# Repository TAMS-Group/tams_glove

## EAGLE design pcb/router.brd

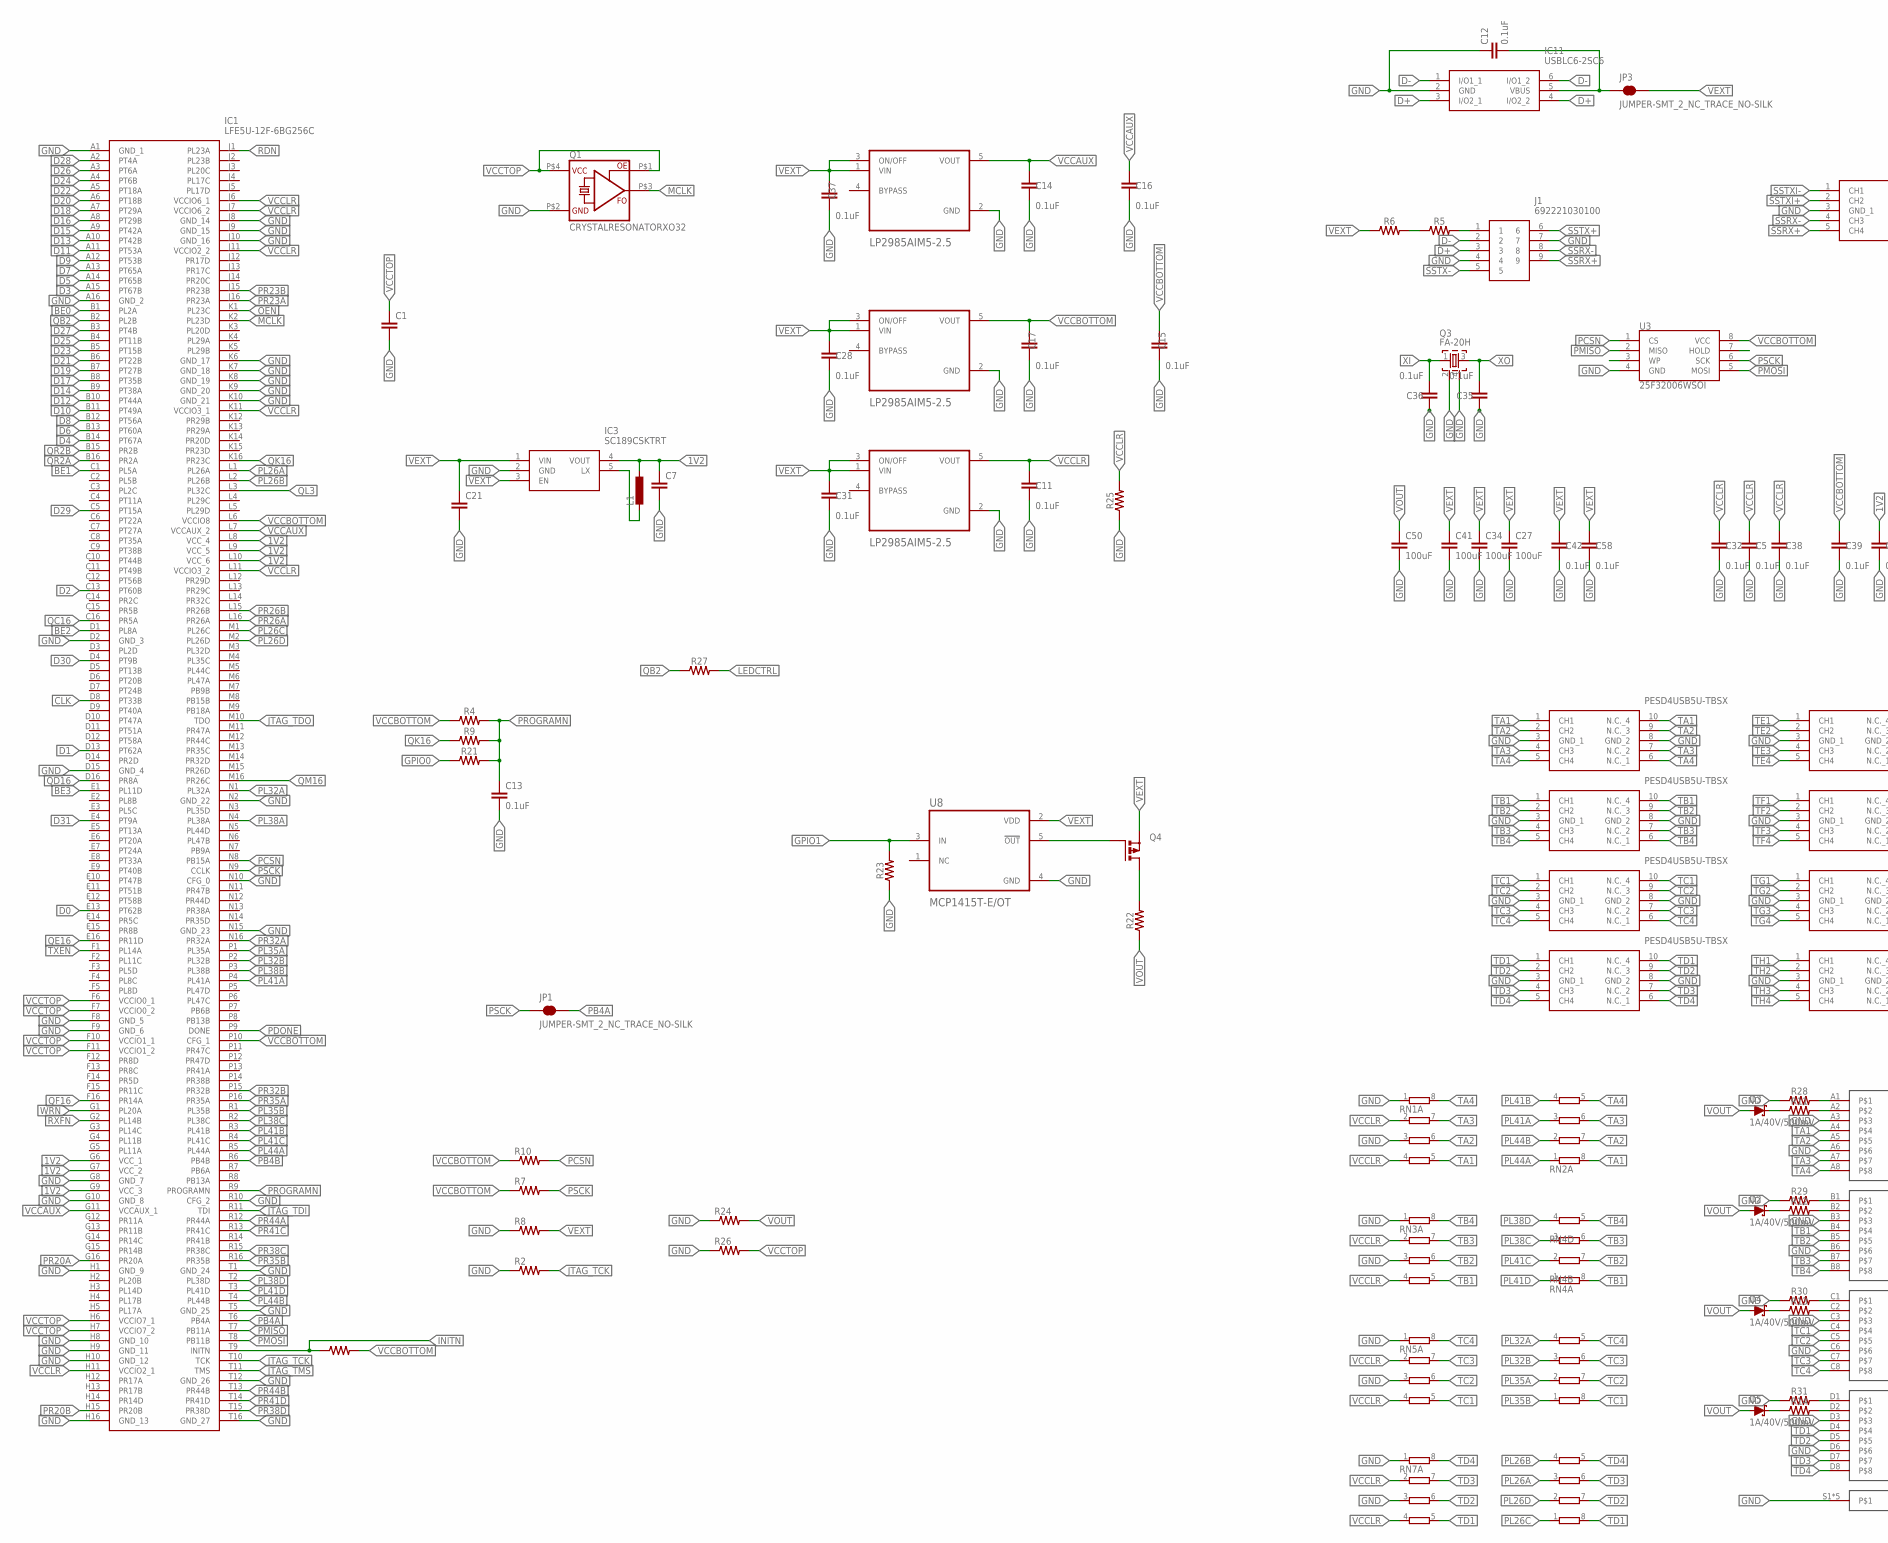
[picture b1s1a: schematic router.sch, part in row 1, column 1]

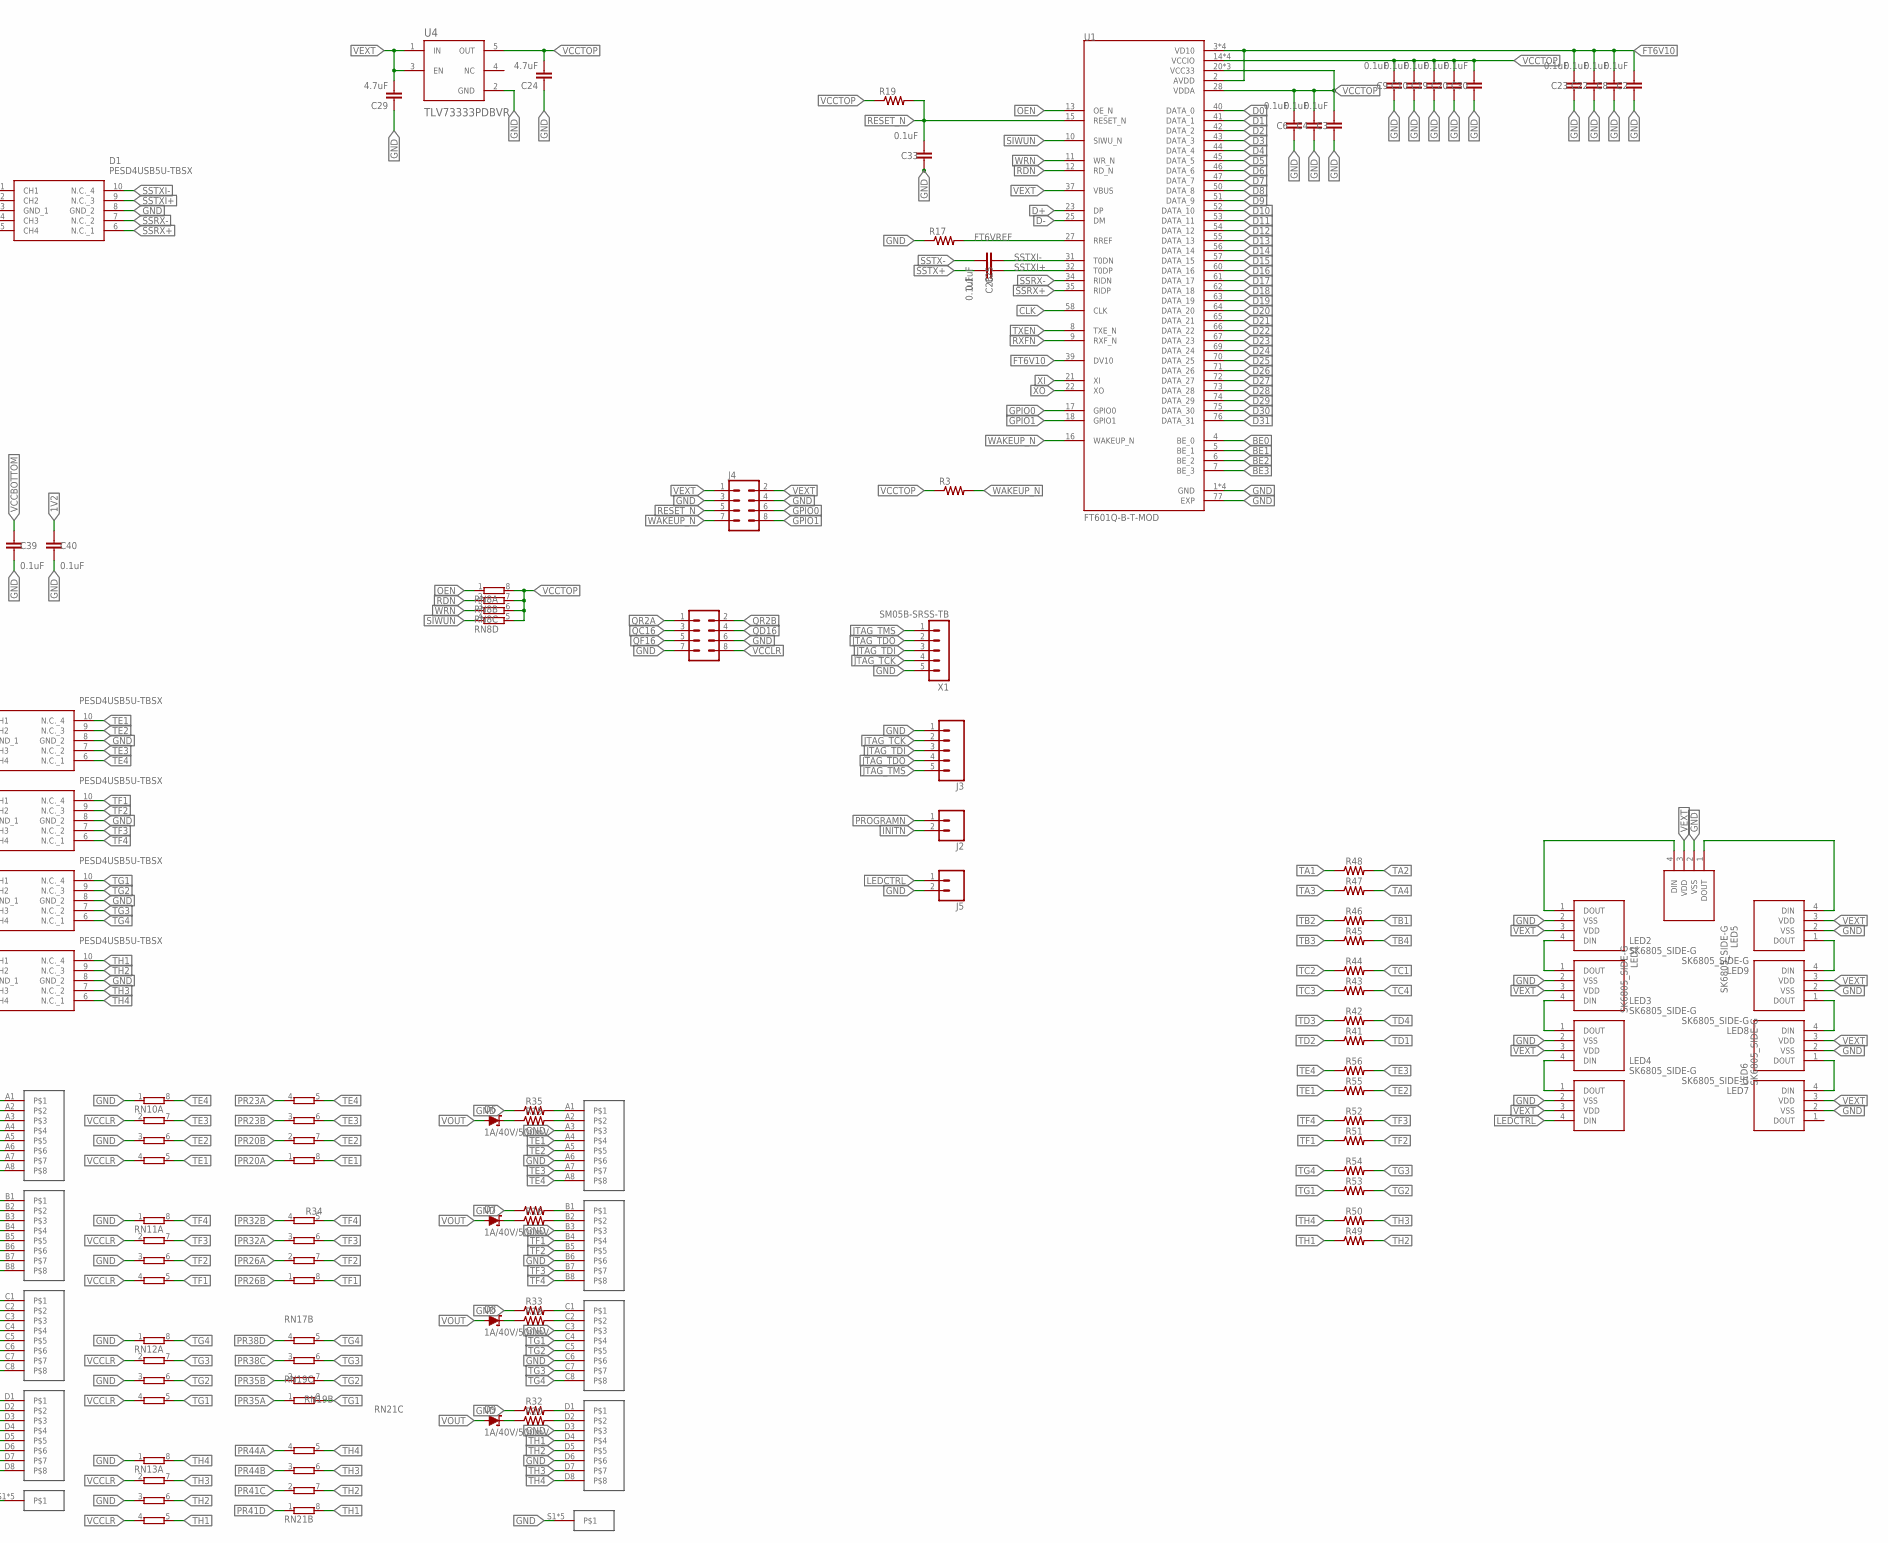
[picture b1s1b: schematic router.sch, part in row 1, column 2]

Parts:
C1: C-EUC0603; C0603
C2, C3, C4, C5, C6, C8, C9, C10, C11, C12, C13, C14, C15, C16, C17, C19, C20, C22, C23, C25, C26, C28, C30, C31, C32, C33, C35, C36, C37, C38, C39, C40, C42, C58: 0.1uF; 0603
C7, C21: C-EUC0805; C0805
C24, C29: 4.7uF; C0603
C27, C34, C41, C50: 100uF; C1210
D1, D10, D11, D12, D13, D14, D15, D16, D17: PESD4USB5U-TBSX; SON50P100X250X80-10N
D2, D3, D4, D5, D6, D7, D8, D9: 1A/40V/500mV; SMA-DIODE
IC1: LFE5U-12F-6BG256C; BGA256C80P16X16_1400X1400X170
IC3: SC189CSKTRT; SOT95P280X145-5N
IC11: USBLC6-2SC6; SOT95P280X145-6N
J1: 692221030100; WR-COM_USB_TYPE_B
J2, J5: CONN_02; 1X02
J3: CONN_05; 1X05
J4, J8: CONN_04X2; 2X4
JP1, JP3: JUMPER-SMT_2_NC_TRACE_NO-SILK; SMT-JUMPER_2_NC_TRACE_NO-SILK
L1: L-EUL3230M; L3230M
LED1, LED2, LED3, LED4, LED5, LED6, LED7, LED8, LED9: SK6805_SIDE-G; SK6805SIDEG
Q1: CRYSTALRESONATORXO32; XO32
Q3: FA-20H
Q4: P-MOSFET-SO8; SO-08
R1, R2, R3, R4, R7, R8, R9, R10, R17, R19, R21, R23, R24, R25, R26, R27, R28, R29, R30, R31, R32, R33, R34, R35: 0603
R5, R6, R11, R12, R13, R14, R15, R16, R18, R20: 0805
R22: 1206
R41, R42, R43, R44, R45, R46, R47, R48, R49, R50, R51, R52, R53, R54, R55, R56: 0402
RN1, RN2, RN3, RN4, RN5, RN6, RN7, RN8, RN9, RN10, RN11, RN12, RN13, RN15, RN17, RN19, RN21: 4R-NEXBV8V; EXBV8V
U1: FT601Q-B-T-MOD; QFN40P900X900X100-77N-MOD
U3: 25F32006WSOI; SO08-EIAJ
U4: TLV73333PDBVR; SOT95P280X145-5N
U5, U6, U7: LP2985AIM5-2.5; SOT95P280X145-5N
U8: MCP1415T-E/OT; SOT95P270X145-5N
U$49, U$50: QUADRJ45; ARJ14A-MESA-MU2_CONN_ARJ14A-MESA-MU2
X1: SM05B-SRSS-TB

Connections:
1V2: C7.1, C40.1, IC1.G6 (VCC_1), IC1.G7 (VCC_2), IC1.G9 (VCC_3), IC1.L8 (VCC_4), IC1.L9 (VCC_5), IC1.L10 (VCC_6), IC3.4 (VOUT), L1.1
BE0: IC1.B1 (PL2A), U1.4 (BE_0)
BE1: IC1.C1 (PL5A), U1.5 (BE_1)
BE2: IC1.D1 (PL8A), U1.6 (BE_2)
BE3: IC1.E1 (PL11D), U1.7 (BE_3)
CLK: IC1.D8 (PT33B), U1.58 (CLK)
D0: IC1.E13 (PT62B), U1.40 (DATA_0)
D1: IC1.D13 (PT62A), U1.41 (DATA_1)
D2: IC1.C13 (PT60B), U1.42 (DATA_2)
D3: IC1.A15 (PT67B), U1.43 (DATA_3)
D4: IC1.B14 (PT67A), U1.44 (DATA_4)
D5: IC1.A14 (PT65B), U1.45 (DATA_5)
D6: IC1.B13 (PT60A), U1.46 (DATA_6)
D7: IC1.A13 (PT65A), U1.47 (DATA_7)
D8: IC1.B12 (PT56A), U1.50 (DATA_8)
D9: IC1.A12 (PT53B), U1.51 (DATA_9)
D10: IC1.B11 (PT49A), U1.52 (DATA_10)
D11: IC1.A11 (PT53A), U1.53 (DATA_11)
D12: IC1.B10 (PT44A), U1.54 (DATA_12)
D13: IC1.A10 (PT42B), U1.55 (DATA_13)
D14: IC1.B9 (PT38A), U1.56 (DATA_14)
D15: IC1.A9 (PT42A), U1.57 (DATA_15)
D16: IC1.A8 (PT29B), U1.60 (DATA_16)
D17: IC1.B8 (PT35B), U1.61 (DATA_17)
D18: IC1.A7 (PT29A), U1.62 (DATA_18)
D19: IC1.B7 (PT27B), U1.63 (DATA_19)
D20: IC1.A6 (PT18B), U1.64 (DATA_20)
D21: IC1.B6 (PT22B), U1.65 (DATA_21)
D22: IC1.A5 (PT18A), U1.66 (DATA_22)
D23: IC1.B5 (PT15B), U1.67 (DATA_23)
D24: IC1.A4 (PT6B), U1.69 (DATA_24)
D25: IC1.B4 (PT11B), U1.70 (DATA_25)
D26: IC1.A3 (PT6A), U1.71 (DATA_26)
D27: IC1.B3 (PT4B), U1.72 (DATA_27)
D28: IC1.A2 (PT4A), U1.73 (DATA_28)
D29: IC1.C5 (PT15A), U1.74 (DATA_29)
D30: IC1.D4 (PT9B), U1.75 (DATA_30)
D31: IC1.E4 (PT9A), U1.76 (DATA_31)
D+: IC11.3 (I/O2_1), IC11.4 (I/O2_2), J1.3, U1.23 (DP)
D-: IC11.1 (I/O1_1), IC11.6 (I/O1_2), J1.2, U1.25 (DM)
FT6V10: C2.2, C8.2, C22.2, C23.2, U1.2 (AVDD), U1.3 (VD10), U1.30 (VD10), U1.33 (VD10), U1.39 (DV10), U1.48 (VD10)
FT6VREF: R17.2, U1.27 (RREF)
GND: C1.2, C2.1, C3.1, C4.1, C5.2, C6.1, C7.2, C8.1, C9.1, C10.1, C11.2, C12.1, C13.2, C14.2, C15.2, C16.2, C17.2, C19.1, C20.1, C21.2, C22.1, C23.1, C24.1, C27.2, C28.2, C29.1, C30.1, C31.2, C32.2, C33.1, C34.2, C35.1, C36.1, C37.2, C38.2, C39.2, C40.2, C41.2, C42.2, C50.2, C58.2, D1.3 (GND_1), D1.8 (GND_2), D10.3 (GND_1), D10.8 (GND_2), D11.3 (GND_1), D11.8 (GND_2), D12.3 (GND_1), D12.8 (GND_2), D13.3 (GND_1), D13.8 (GND_2), D14.3 (GND_1), D14.8 (GND_2), D15.3 (GND_1), D15.8 (GND_2), D16.3 (GND_1), D16.8 (GND_2), D17.3 (GND_1), D17.8 (GND_2), IC1.A1 (GND_1), IC1.A16 (GND_2), IC1.D2 (GND_3), IC1.D15 (GND_4), IC1.F8 (GND_5), IC1.F9 (GND_6), IC1.G8 (GND_7), IC1.G10 (GND_8), IC1.H1 (GND_9), IC1.H8 (GND_10), IC1.H9 (GND_11), IC1.H10 (GND_12), IC1.H16 (GND_13), IC1.J8 (GND_14), IC1.J9 (GND_15), IC1.J10 (GND_16), IC1.K6 (GND_17), IC1.K7 (GND_18), IC1.K8 (GND_19), IC1.K9 (GND_20), IC1.K10 (GND_21), IC1.N2 (GND_22), IC1.N10 (CFG_0), IC1.N15 (GND_23), IC1.R10 (CFG_2), IC1.T1 (GND_24), IC1.T5 (GND_25), IC1.T12 (GND_26), IC1.T16 (GND_27), IC3.2 (GND), IC11.2 (GND), J1.4, J1.7, J3.1, J4.3, J4.4, J5.2, J8.6, J8.7, LED1.2 (VSS), LED2.2 (VSS), LED3.2 (VSS), LED4.2 (VSS), LED5.2 (VSS), LED6.2 (VSS), LED7.2 (VSS), LED8.2 (VSS), LED9.2 (VSS), Q1.P$2 (GND), Q3.2, Q3.4, R2.1, R8.1, R17.1, R23.1, R24.1, R25.1, R26.1, R28.1, R29.1, R30.1, R31.1, R32.1, R33.1, R34.1, R35.1, RN1.1, RN1.3 (1), RN3.1, RN3.3 (1), RN5.1, RN5.3 (1), RN7.1, RN7.3 (1), RN10.1, RN10.3 (1), RN11.1, RN11.3 (1), RN12.1, RN12.3 (1), RN13.1, RN13.3 (1), U1.1 (GND), U1.26 (GND), U1.29 (GND), U1.36 (GND), U1.77 (EXP), U3.4 (GND), U4.2 (GND), U5.2 (GND), U6.2 (GND), U7.2 (GND), U8.4 (GND), U$49.A3, U$49.A6, U$49.B3, U$49.B6, U$49.C3, U$49.C6, U$49.D3, U$49.D6, U$49.S1, U$49.S2, U$49.S3, U$49.S4, U$49.S5, U$50.A3, U$50.A6, U$50.B3, U$50.B6, U$50.C3, U$50.C6, U$50.D3, U$50.D6, U$50.S1, U$50.S2, U$50.S3, U$50.S4, U$50.S5, X1.5
GPIO0: J4.6, R21.1, U1.17 (GPIO0)
GPIO1: J4.8, R23.2, U1.18 (GPIO1), U8.3 (IN)
INITN: IC1.T9 (INITN), J2.2, R1.1
JTAG_TCK: IC1.T10 (TCK), J3.2, R2.2, X1.4
JTAG_TDI: IC1.R11 (TDI), J3.3, X1.3
JTAG_TDO: IC1.M10 (TDO), J3.4, X1.2
JTAG_TMS: IC1.T11 (TMS), J3.5, X1.1
LEDCTRL: J5.1, LED4.4 (DIN), R27.2
MCLK: IC1.K2 (PL23D), Q1.P$3 (FO)
unnamed: R15.2, U$50.A2
unnamed: R16.2, U$50.B2
unnamed: IC3.5 (LX), L1.2
unnamed: R18.2, U$50.C2
unnamed: R20.2, U$50.D2
unnamed: R35.2, U$50.A1
unnamed: C12.2, IC11.5 (VBUS), JP3.1
unnamed: R5.1, R6.2
unnamed: J1.1, R5.2
unnamed: Q4.4 (G), U8.5 (!OUT)
unnamed: Q4.5 (D), Q4.6 (D), Q4.7 (D), Q4.8 (D), R22.2
unnamed: R34.2, U$50.B1
unnamed: R33.2, U$50.C1
unnamed: LED1.4 (DIN), LED2.1 (DOUT)
unnamed: R32.2, U$50.D1
unnamed: R11.2, U$49.A2
unnamed: R12.2, U$49.B2
unnamed: R13.2, U$49.C2
unnamed: LED2.4 (DIN), LED3.1 (DOUT)
unnamed: R14.2, U$49.D2
unnamed: LED3.4 (DIN), LED4.1 (DOUT)
unnamed: R28.2, U$49.A1
unnamed: LED6.4 (DIN), LED7.1 (DOUT)
unnamed: D3.C, R11.1
unnamed: LED1.1 (DOUT), LED5.4 (DIN)
unnamed: R29.2, U$49.B1
unnamed: LED7.4 (DIN), LED8.1 (DOUT)
unnamed: R30.2, U$49.C1
unnamed: R31.2, U$49.D1
unnamed: LED8.4 (DIN), LED9.1 (DOUT)
unnamed: LED5.1 (DOUT), LED9.4 (DIN)
unnamed: D2.C, R12.1
unnamed: D4.C, R13.1
unnamed: D5.C, R14.1
unnamed: D6.C, R15.1
unnamed: D7.C, R16.1
unnamed: D8.C, R18.1
unnamed: D9.C, R20.1
OEN: IC1.K1 (PL23C), RN8.1, U1.13 (OE_N)
PB4A: IC1.T6 (PB4A), JP1.2
PB4B: IC1.R6 (PB4B)
PCSN: IC1.N8 (PB15A), R10.2, U3.1 (CS)
PDONE: IC1.P9 (DONE)
PL26A: IC1.L1 (PL26A), RN9.3 (1)
PL26B: IC1.L2 (PL26B), RN9.4 (1)
PL26C: IC1.M1 (PL26C), RN9.1
PL26D: IC1.M2 (PL26D), RN9.2 (1)
PL32A: IC1.N1 (PL32A), RN6.4 (1)
PL32B: IC1.P2 (PL32B), RN6.3 (1)
PL35A: IC1.P1 (PL35A), RN6.2 (1)
PL35B: IC1.R1 (PL35B), RN6.1
PL38A: IC1.N4 (PL38A)
PL38B: IC1.P3 (PL38B)
PL38C: IC1.R2 (PL38C), RN4.3 (1)
PL38D: IC1.T2 (PL38D), RN4.4 (1)
PL41A: IC1.P4 (PL41A), RN2.3 (1)
PL41B: IC1.R3 (PL41B), RN2.4 (1)
PL41C: IC1.R4 (PL41C), RN4.2 (1)
PL41D: IC1.T3 (PL41D), RN4.1
PL44A: IC1.R5 (PL44A), RN2.1
PL44B: IC1.T4 (PL44B), RN2.2 (1)
PMISO: IC1.T7 (PB11A), U3.2 (MISO)
PMOSI: IC1.T8 (PB11B), U3.5 (MOSI)
PR20A: IC1.G16 (PR20A), RN15.1
PR20B: IC1.H15 (PR20B), RN15.2 (1)
PR23A: IC1.J16 (PR23A), RN15.4 (1)
PR23B: IC1.J15 (PR23B), RN15.3 (1)
PR26A: IC1.L16 (PR26A), RN17.2 (1)
PR26B: IC1.L15 (PR26B), RN17.1
PR32A: IC1.N16 (PR32A), RN17.3 (1)
PR32B: IC1.P15 (PR32B), RN17.4 (1)
PR35A: IC1.P16 (PR35A), RN19.1
PR35B: IC1.R16 (PR35B), RN19.2 (1)
PR38C: IC1.R15 (PR38C), RN19.3 (1)
PR38D: IC1.T15 (PR38D), RN19.4 (1)
PR41C: IC1.R13 (PR41C), RN21.2 (1)
PR41D: IC1.T14 (PR41D), RN21.1
PR44A: IC1.R12 (PR44A), RN21.4 (1)
PR44B: IC1.T13 (PR44B), RN21.3 (1)
PROGRAMN: C13.1, IC1.R9 (PROGRAMN), J2.1, R4.2, R9.2, R21.2
PSCK: IC1.N9 (CCLK), JP1.1, R7.2, U3.6 (SCK)
QB2: IC1.B2 (PL2B), R27.1
QC16: IC1.C16 (PR5A), J8.3
QD16: IC1.D16 (PR8A), J8.4
QE16: IC1.E16 (PR11D)
QF16: IC1.F16 (PR14A), J8.5
QK16: IC1.K16 (PR23C), R9.1
QL3: IC1.L3 (PL32C)
QM16: IC1.M16 (PR26C)
QR2A: IC1.B16 (PR2A), J8.1
QR2B: IC1.B15 (PR2B), J8.2
RDN: IC1.J1 (PL23A), RN8.2 (1), U1.12 (RD_N)
RESET_N: C33.2, J4.5, R19.2, U1.15 (RESET_N)
RXFN: IC1.G2 (PL14B), U1.9 (RXF_N)
SIWUN: RN8.4 (1), U1.10 (SIWU_N)
SSRX+: D1.5 (CH4), D1.6 (N.C._1), J1.9, U1.35 (RIDP)
SSRX-: D1.4 (CH3), D1.7 (N.C._2), J1.8, U1.34 (RIDN)
SSTX+: C26.2, J1.6
SSTX-: C25.2, J1.5
SSTXI+: C26.1, D1.2 (CH2), D1.9 (N.C._3), U1.32 (T0DP)
SSTXI-: C25.1, D1.1 (CH1), D1.10 (N.C._4), U1.31 (T0DN)
TA1: D10.1 (CH1), D10.10 (N.C._4), R48.1, RN1.5 (2), RN2.8 (2), U$49.A4
TA2: D10.2 (CH2), D10.9 (N.C._3), R48.2, RN1.6 (2), RN2.7 (2), U$49.A5
TA3: D10.4 (CH3), D10.7 (N.C._2), R47.1, RN1.7 (2), RN2.6 (2), U$49.A7
TA4: D10.5 (CH4), D10.6 (N.C._1), R47.2, RN1.8 (2), RN2.5 (2), U$49.A8
TB1: D11.1 (CH1), D11.10 (N.C._4), R46.2, RN3.5 (2), RN4.8 (2), U$49.B4
TB2: D11.2 (CH2), D11.9 (N.C._3), R46.1, RN3.6 (2), RN4.7 (2), U$49.B5
TB3: D11.4 (CH3), D11.7 (N.C._2), R45.1, RN3.7 (2), RN4.6 (2), U$49.B7
TB4: D11.5 (CH4), D11.6 (N.C._1), R45.2, RN3.8 (2), RN4.5 (2), U$49.B8
TC1: D12.1 (CH1), D12.10 (N.C._4), R44.2, RN5.5 (2), RN6.8 (2), U$49.C4
TC2: D12.2 (CH2), D12.9 (N.C._3), R44.1, RN5.6 (2), RN6.7 (2), U$49.C5
TC3: D12.4 (CH3), D12.7 (N.C._2), R43.1, RN5.7 (2), RN6.6 (2), U$49.C7
TC4: D12.5 (CH4), D12.6 (N.C._1), R43.2, RN5.8 (2), RN6.5 (2), U$49.C8
TD1: D13.1 (CH1), D13.10 (N.C._4), R41.2, RN7.5 (2), RN9.8 (2), U$49.D4
TD2: D13.2 (CH2), D13.9 (N.C._3), R41.1, RN7.6 (2), RN9.7 (2), U$49.D5
TD3: D13.4 (CH3), D13.7 (N.C._2), R42.1, RN7.7 (2), RN9.6 (2), U$49.D7
TD4: D13.5 (CH4), D13.6 (N.C._1), R42.2, RN7.8 (2), RN9.5 (2), U$49.D8
TE1: D14.1 (CH1), D14.10 (N.C._4), R55.1, RN10.5 (2), RN15.8 (2), U$50.A4
TE2: D14.2 (CH2), D14.9 (N.C._3), R55.2, RN10.6 (2), RN15.7 (2), U$50.A5
TE3: D14.4 (CH3), D14.7 (N.C._2), R56.2, RN10.7 (2), RN15.6 (2), U$50.A7
TE4: D14.5 (CH4), D14.6 (N.C._1), R56.1, RN10.8 (2), RN15.5 (2), U$50.A8
TF1: D15.1 (CH1), D15.10 (N.C._4), R51.1, RN11.5 (2), RN17.8 (2), U$50.B4
TF2: D15.2 (CH2), D15.9 (N.C._3), R51.2, RN11.6 (2), RN17.7 (2), U$50.B5
TF3: D15.4 (CH3), D15.7 (N.C._2), R52.2, RN11.7 (2), RN17.6 (2), U$50.B7
TF4: D15.5 (CH4), D15.6 (N.C._1), R52.1, RN11.8 (2), RN17.5 (2), U$50.B8
TG1: D16.1 (CH1), D16.10 (N.C._4), R53.1, RN12.5 (2), RN19.8 (2), U$50.C4
TG2: D16.2 (CH2), D16.9 (N.C._3), R53.2, RN12.6 (2), RN19.7 (2), U$50.C5
TG3: D16.4 (CH3), D16.7 (N.C._2), R54.2, RN12.7 (2), RN19.6 (2), U$50.C7
TG4: D16.5 (CH4), D16.6 (N.C._1), R54.1, RN12.8 (2), RN19.5 (2), U$50.C8
TH1: D17.1 (CH1), D17.10 (N.C._4), R49.1, RN13.5 (2), RN21.8 (2), U$50.D4
TH2: D17.2 (CH2), D17.9 (N.C._3), R49.2, RN13.6 (2), RN21.7 (2), U$50.D5
TH3: D17.4 (CH3), D17.7 (N.C._2), R50.2, RN13.7 (2), RN21.6 (2), U$50.D7
TH4: D17.5 (CH4), D17.6 (N.C._1), R50.1, RN13.8 (2), RN21.5 (2), U$50.D8
TXEN: IC1.F1 (PL14A), U1.8 (TXE_N)
VCCAUX: C14.1, C16.1, IC1.G11 (VCCAUX_1), IC1.L7 (VCCAUX_2), U6.5 (VOUT)
VCCBOTTOM: C15.1, C17.1, C39.1, IC1.L6 (VCCIO8), IC1.P10 (CFG_1), R1.2, R4.1, R7.1, R10.1, U3.8 (VCC), U7.5 (VOUT)
VCCLR: C5.1, C11.1, C32.1, C38.1, IC1.H11 (VCCIO2_1), IC1.J6 (VCCIO6_1), IC1.J7 (VCCIO6_2), IC1.J11 (VCCIO2_2), IC1.K11 (VCCIO3_1), IC1.L11 (VCCIO3_2), J8.8, R25.2, RN1.2 (1), RN1.4 (1), RN3.2 (1), RN3.4 (1), RN5.2 (1), RN5.4 (1), RN7.2 (1), RN7.4 (1), RN10.2 (1), RN10.4 (1), RN11.2 (1), RN11.4 (1), RN12.2 (1), RN12.4 (1), RN13.2 (1), RN13.4 (1), U5.5 (VOUT)
VCCTOP: C1.1, C3.2, C4.2, C6.2, C9.2, C10.2, C19.2, C20.2, C24.2, C30.2, IC1.F6 (VCCIO0_1), IC1.F7 (VCCIO0_2), IC1.F10 (VCCIO1_1), IC1.F11 (VCCIO1_2), IC1.H6 (VCCIO7_1), IC1.H7 (VCCIO7_2), Q1.P$1 (OE), Q1.P$4 (VCC), R3.1, R19.1, R26.2, RN8.5 (2), RN8.6 (2), RN8.7 (2), RN8.8 (2), U1.14 (VCCIO), U1.20 (VCC33), U1.24 (VCC33), U1.28 (VDDA), U1.38 (VCC33), U1.49 (VCCIO), U1.59 (VCCIO), U1.68 (VCCIO), U4.5 (OUT)
VEXT: C21.1, C27.1, C28.1, C29.2, C31.1, C34.1, C37.1, C41.1, C42.1, C58.1, IC3.1 (VIN), IC3.3 (EN), J4.1, J4.2, JP3.2, LED1.3 (VDD), LED2.3 (VDD), LED3.3 (VDD), LED4.3 (VDD), LED5.3 (VDD), LED6.3 (VDD), LED7.3 (VDD), LED8.3 (VDD), LED9.3 (VDD), Q4.1 (S), Q4.2 (S), Q4.3 (S), R6.1, R8.2, U1.37 (VBUS), U4.1 (IN), U4.3 (EN), U5.1 (VIN), U5.3 (ON/OFF), U6.1 (VIN), U6.3 (ON/OFF), U7.1 (VIN), U7.3 (ON/OFF), U8.2 (VDD)
VOUT: C50.1, D2.A, D3.A, D4.A, D5.A, D6.A, D7.A, D8.A, D9.A, R22.1, R24.2
WAKEUP_N: J4.7, R3.2, U1.16 (WAKEUP_N)
WRN: IC1.G1 (PL20A), RN8.3 (1), U1.11 (WR_N)
XI: C36.2, Q3.1, U1.21 (XI)
XO: C35.2, Q3.3, U1.22 (XO)

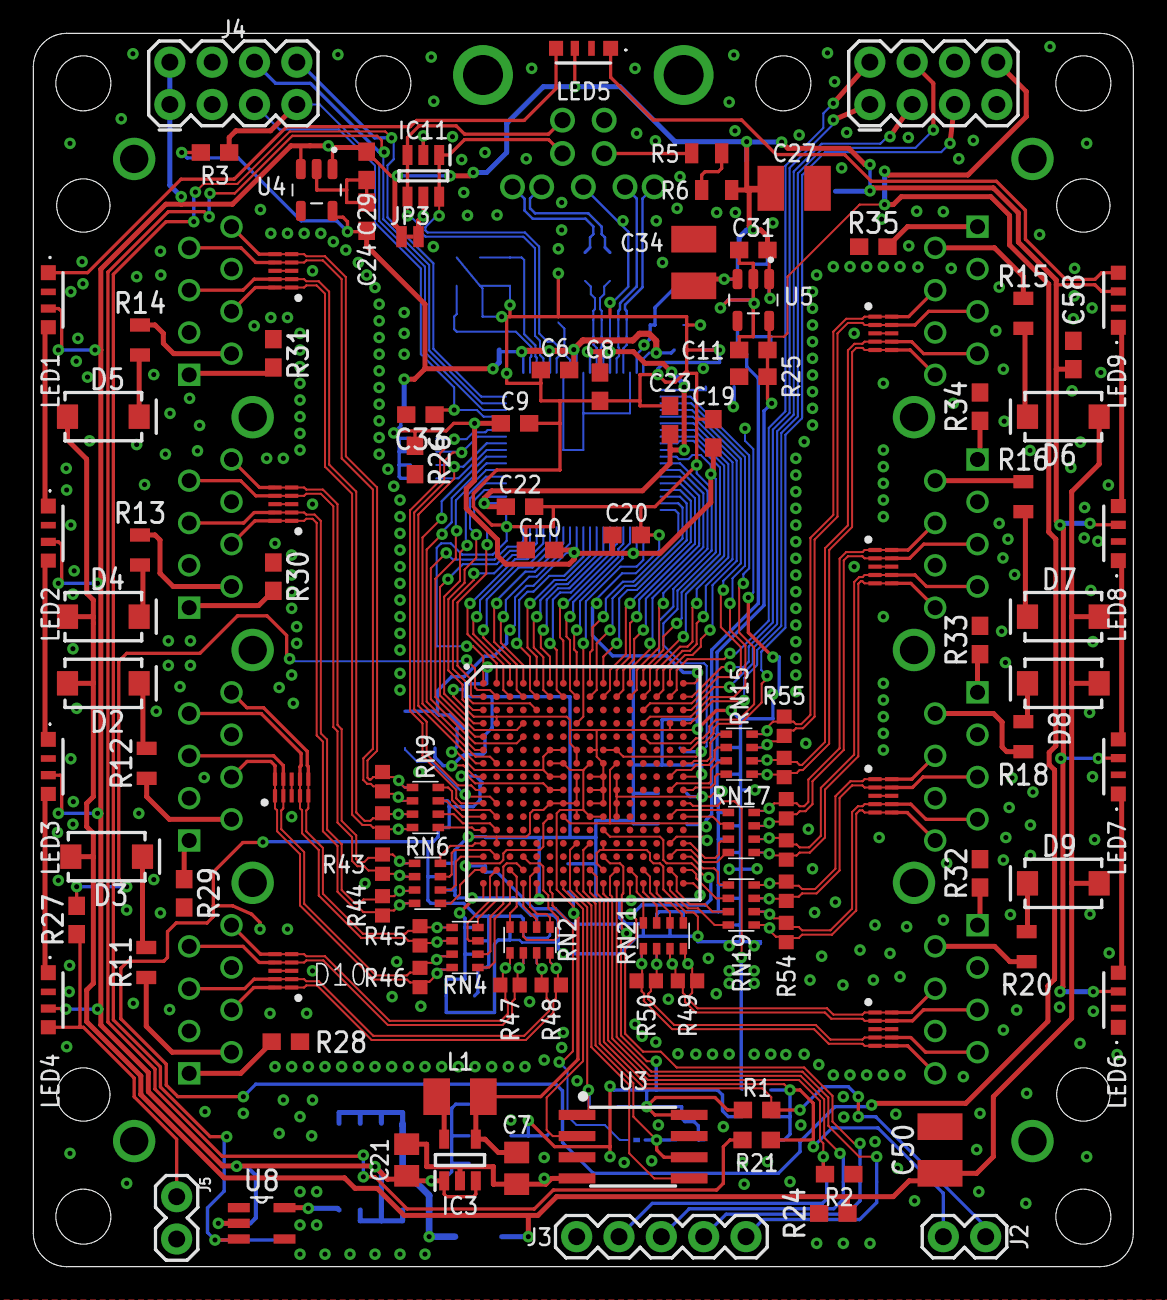
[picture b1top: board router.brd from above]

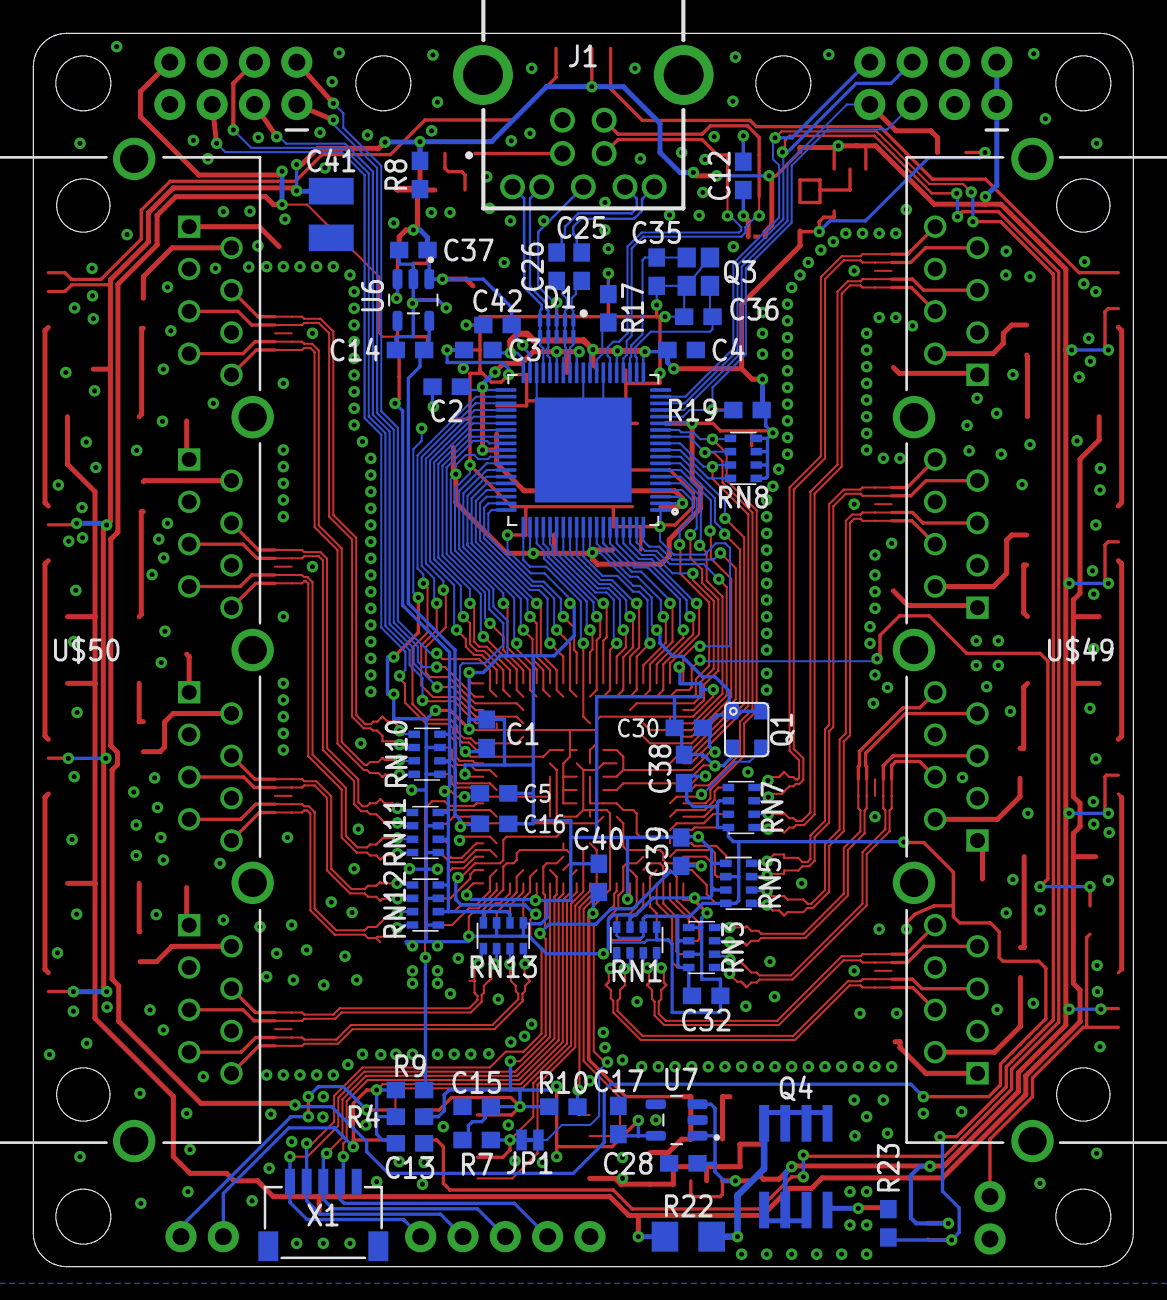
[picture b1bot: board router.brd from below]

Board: 2 copper layers, 66.0 x 74.0 mm, 162 parts (54 on the bottom side), 189 nets.

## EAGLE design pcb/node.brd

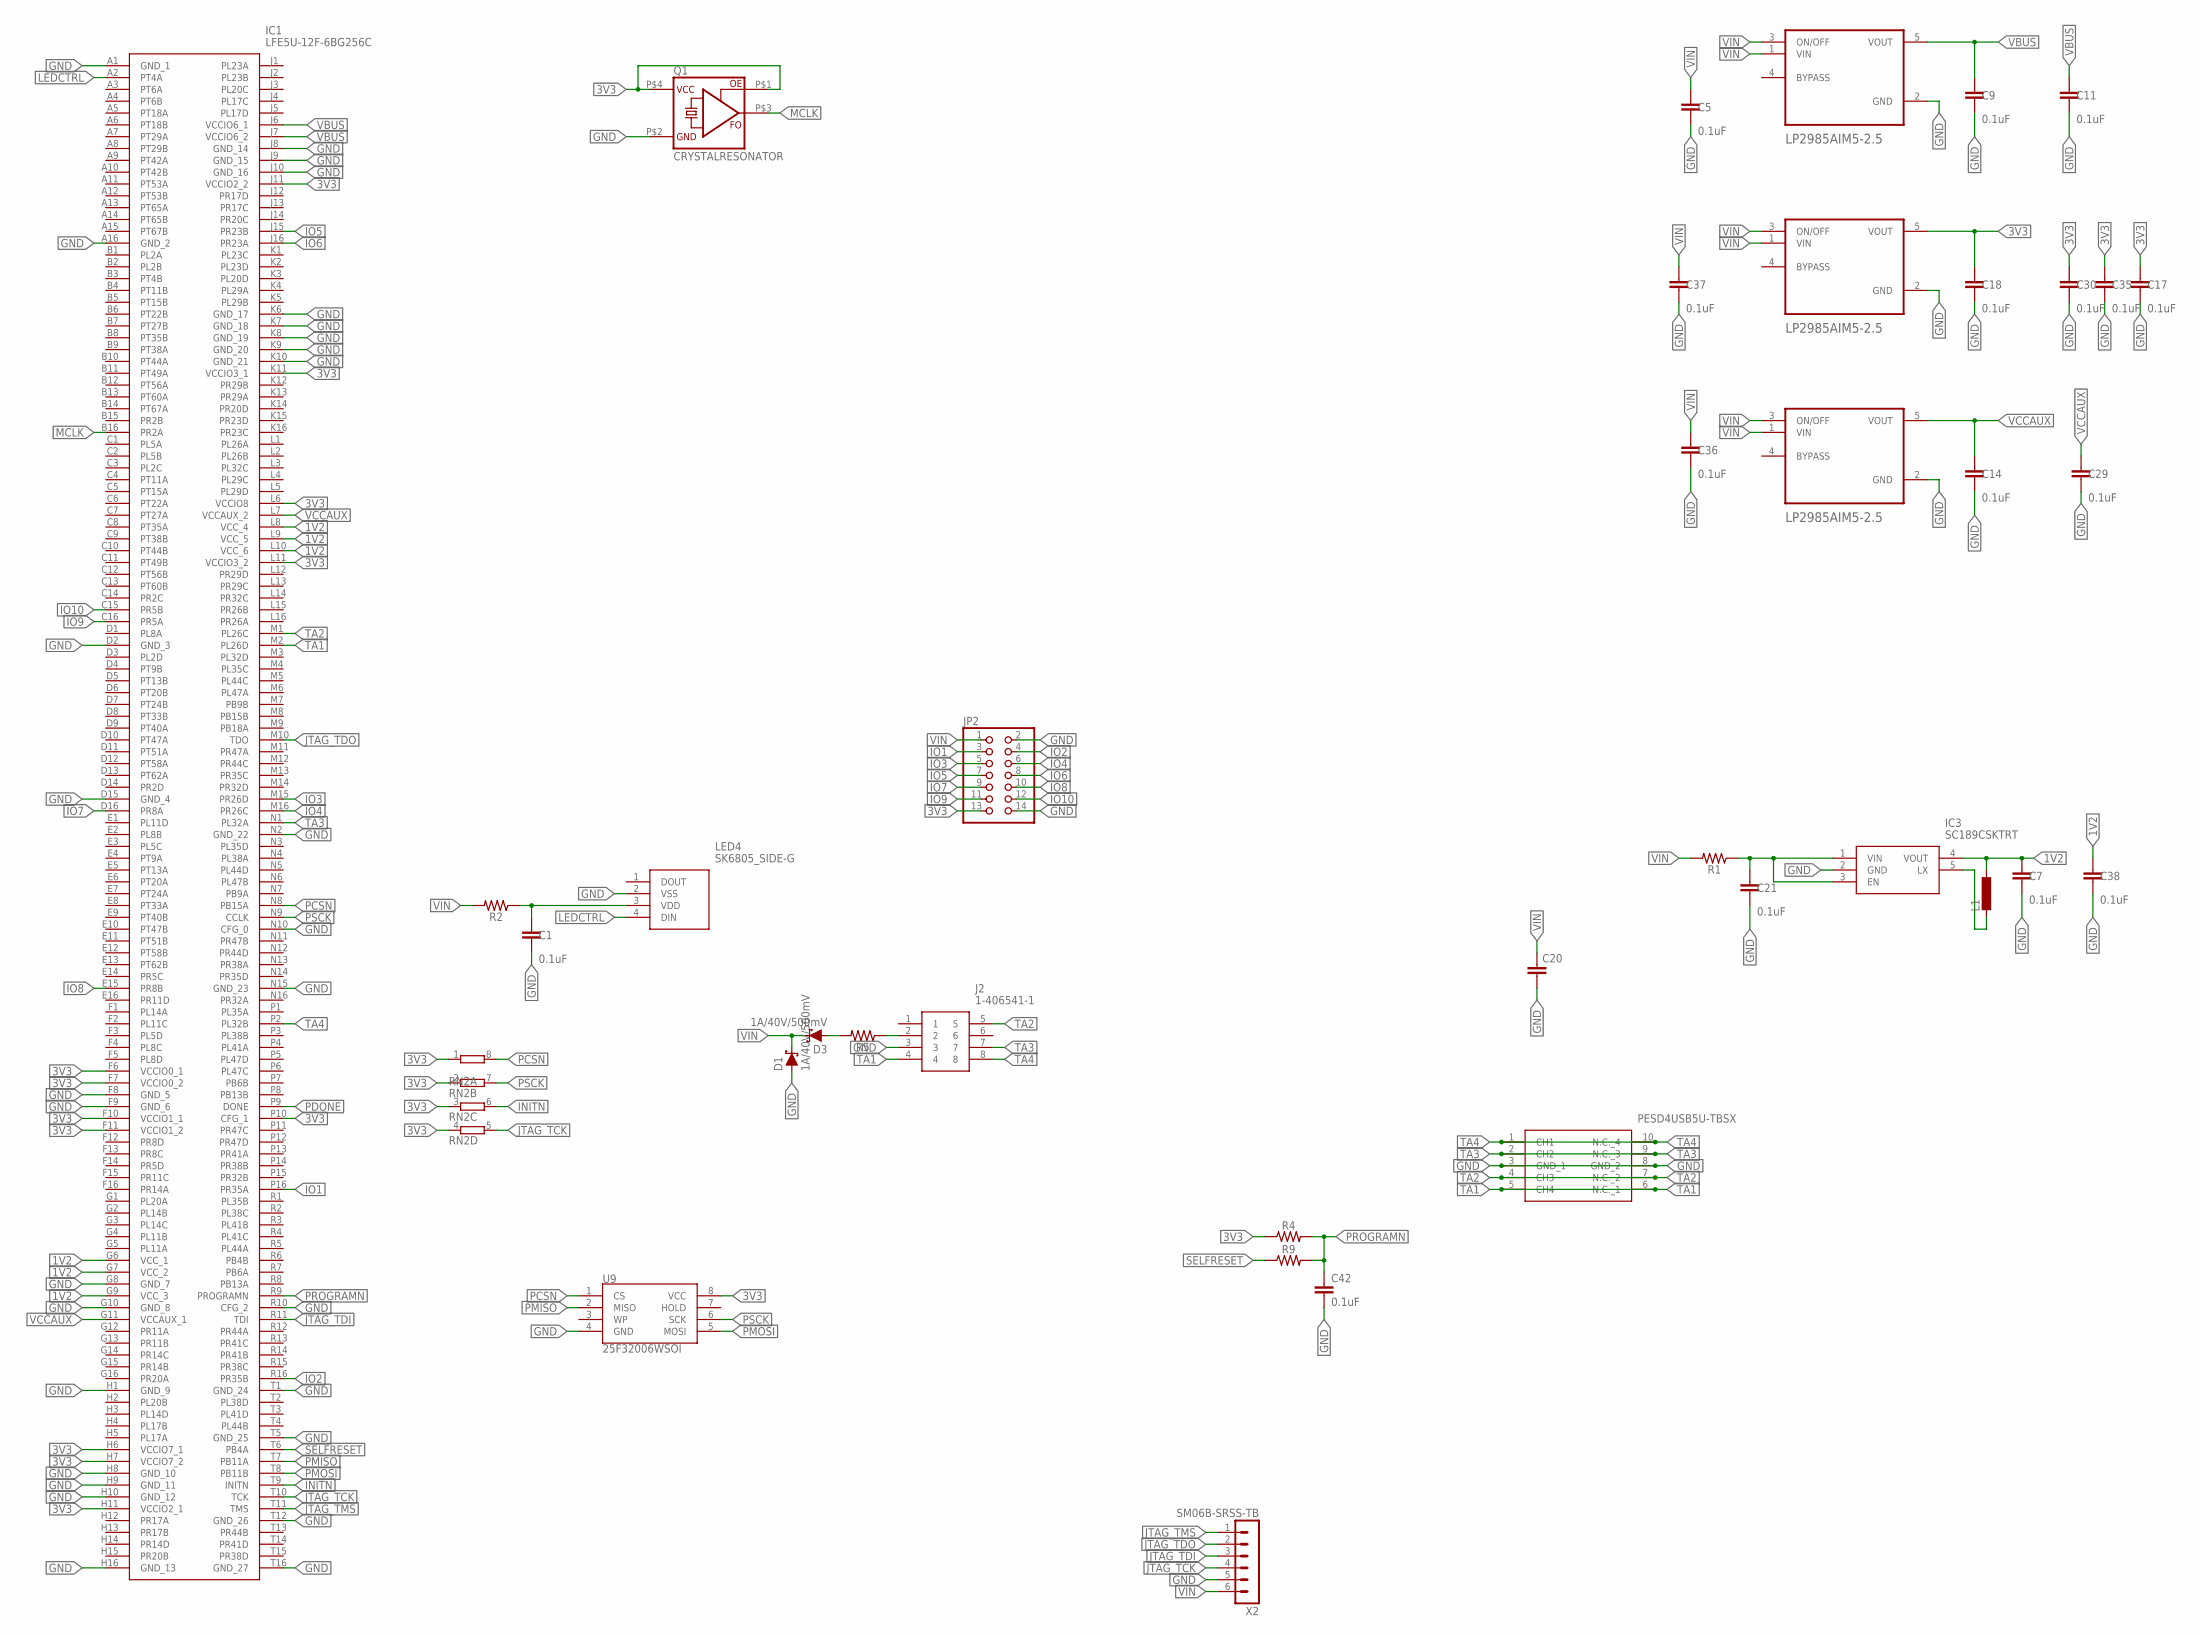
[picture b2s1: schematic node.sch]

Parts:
C1, C5, C7, C9, C11, C14, C17, C18, C21, C29, C30, C35, C36, C37, C38, C42: 0.1uF; 0603
C20: C-EUC1812; C1812
D1, D3: 1A/40V/500mV; SMA-DIODE
D10: PESD4USB5U-TBSX; SON50P100X250X80-10N
IC1: LFE5U-12F-6BG256C; BGA256C80P16X16_1400X1400X170
IC3: SC189CSKTRT; SOT95P280X145-5N
J2: 1-406541-1; 1-406541-1_1
JP2: PINHD-2X7; 2X07
L1: L-EUL3230M; L3230M
LED4: SK6805_SIDE-G; SK6805SIDEG
Q1: CRYSTALRESONATOR; XO53X
R1, R2, R4, R9: 0603
R5: 0805
RN2: 4R-NEXBV8V; EXBV8V
U1, U2, U6: LP2985AIM5-2.5; SOT95P280X145-5N
U9: 25F32006WSOI; SO08-EIAJ
X2: SM06B-SRSS-TB

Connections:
1V2: C7.1, C38.1, IC1.G6 (VCC_1), IC1.G7 (VCC_2), IC1.G9 (VCC_3), IC1.L8 (VCC_4), IC1.L9 (VCC_5), IC1.L10 (VCC_6), IC3.4 (VOUT), L1.1
3V3: C17.1, C18.1, C30.1, C35.1, IC1.F6 (VCCIO0_1), IC1.F7 (VCCIO0_2), IC1.F10 (VCCIO1_1), IC1.F11 (VCCIO1_2), IC1.H6 (VCCIO7_1), IC1.H7 (VCCIO7_2), IC1.H11 (VCCIO2_1), IC1.J11 (VCCIO2_2), IC1.K11 (VCCIO3_1), IC1.L6 (VCCIO8), IC1.L11 (VCCIO3_2), IC1.P10 (CFG_1), JP2.13, Q1.P$1 (OE), Q1.P$4 (VCC), R4.1, RN2.1, RN2.2 (1), RN2.3 (1), RN2.4 (1), U2.5 (VOUT), U9.8 (VCC)
GND: C1.2, C5.2, C7.2, C9.2, C11.2, C14.2, C17.2, C18.2, C20.2, C21.2, C29.2, C30.2, C35.2, C36.2, C37.2, C38.2, C42.2, D1.A, D10.3 (GND_1), D10.8 (GND_2), IC1.A1 (GND_1), IC1.A16 (GND_2), IC1.D2 (GND_3), IC1.D15 (GND_4), IC1.F8 (GND_5), IC1.F9 (GND_6), IC1.G8 (GND_7), IC1.G10 (GND_8), IC1.H1 (GND_9), IC1.H8 (GND_10), IC1.H9 (GND_11), IC1.H10 (GND_12), IC1.H16 (GND_13), IC1.J8 (GND_14), IC1.J9 (GND_15), IC1.J10 (GND_16), IC1.K6 (GND_17), IC1.K7 (GND_18), IC1.K8 (GND_19), IC1.K9 (GND_20), IC1.K10 (GND_21), IC1.N2 (GND_22), IC1.N10 (CFG_0), IC1.N15 (GND_23), IC1.R10 (CFG_2), IC1.T1 (GND_24), IC1.T5 (GND_25), IC1.T12 (GND_26), IC1.T16 (GND_27), IC3.2 (GND), J2.3, JP2.2, JP2.14, LED4.2 (VSS), Q1.P$2 (GND), U1.2 (GND), U2.2 (GND), U6.2 (GND), U9.4 (GND), X2.5
INITN: IC1.T9 (INITN), RN2.6 (2)
IO1: IC1.P16 (PR35A), JP2.3
IO2: IC1.R16 (PR35B), JP2.4
IO3: IC1.M15 (PR26D), JP2.5
IO4: IC1.M16 (PR26C), JP2.6
IO5: IC1.J15 (PR23B), JP2.7
IO6: IC1.J16 (PR23A), JP2.8
IO7: IC1.D16 (PR8A), JP2.9
IO8: IC1.E15 (PR8B), JP2.10
IO9: IC1.C16 (PR5A), JP2.11
IO10: IC1.C15 (PR5B), JP2.12
JTAG_TCK: IC1.T10 (TCK), RN2.5 (2), X2.4
JTAG_TDI: IC1.R11 (TDI), X2.3
JTAG_TDO: IC1.M10 (TDO), X2.2
JTAG_TMS: IC1.T11 (TMS), X2.1
LEDCTRL: IC1.A2 (PT4A), LED4.4 (DIN)
MCLK: IC1.B16 (PR2A), Q1.P$3 (FO)
unnamed: C1.1, LED4.3 (VDD), R2.1
unnamed: IC3.5 (LX), L1.2
unnamed: C21.1, IC3.1 (VIN), IC3.3 (EN), R1.1
unnamed: J2.2, R5.1
unnamed: D3.A, R5.2
PCSN: IC1.N8 (PB15A), RN2.8 (2), U9.1 (CS)
PDONE: IC1.P9 (DONE)
PMISO: IC1.T7 (PB11A), U9.2 (MISO)
PMOSI: IC1.T8 (PB11B), U9.5 (MOSI)
PROGRAMN: C42.1, IC1.R9 (PROGRAMN), R4.2, R9.2
PSCK: IC1.N9 (CCLK), RN2.7 (2), U9.6 (SCK)
SELFRESET: IC1.T6 (PB4A), R9.1
TA1: D10.5 (CH4), D10.6 (N.C._1), IC1.M2 (PL26D), J2.4
TA2: D10.4 (CH3), D10.7 (N.C._2), IC1.M1 (PL26C), J2.5
TA3: D10.2 (CH2), D10.9 (N.C._3), IC1.N1 (PL32A), J2.7
TA4: D10.1 (CH1), D10.10 (N.C._4), IC1.P2 (PL32B), J2.8
VBUS: C9.1, C11.1, IC1.J6 (VCCIO6_1), IC1.J7 (VCCIO6_2), U1.5 (VOUT)
VCCAUX: C14.1, C29.1, IC1.G11 (VCCAUX_1), IC1.L7 (VCCAUX_2), U6.5 (VOUT)
VIN: C5.1, C20.1, C36.1, C37.1, D1.C, D3.C, JP2.1, R1.2, R2.2, U1.1 (VIN), U1.3 (ON/OFF), U2.1 (VIN), U2.3 (ON/OFF), U6.1 (VIN), U6.3 (ON/OFF), X2.6

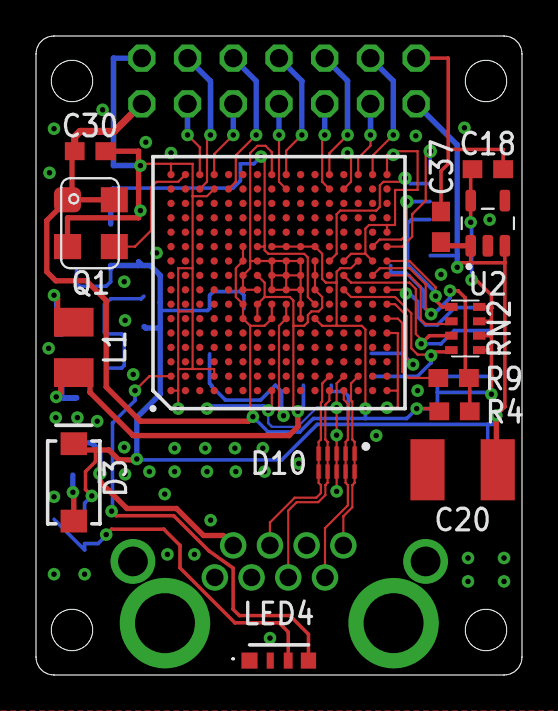
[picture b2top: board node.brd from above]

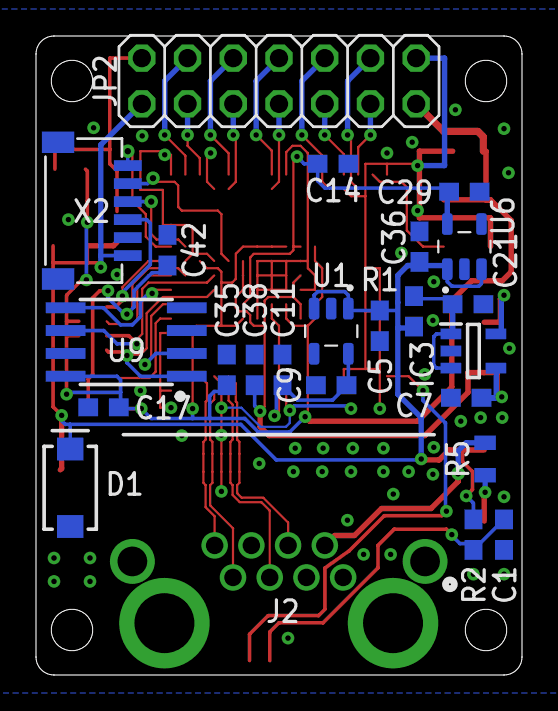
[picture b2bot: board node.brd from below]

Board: 2 copper layers, 27.0 x 35.5 mm, 38 parts (24 on the bottom side), 38 nets.

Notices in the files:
parts and their libraries:
SparkFun-Capacitors: Licensing: Creative Commons ShareAlike 4.0 International - https://creativecommons.org/licenses/by-sa/4.0
